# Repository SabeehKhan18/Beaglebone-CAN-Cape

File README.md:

# Beaglebone CAN Cape
Simple CAN cape for the Beaglebone Black

This is a CAN transceiver evaluation board that can be used to develop a CAN bus or even to sniff a vehicle's CAN bus. By using an SOIC-8 breakout board, and adjusting the pin jumpers provided on the cape, any 3.3V or 5V SOIC-8 CAN transceiver can be tested.
A demo of our project can be found on youtube:
https://youtu.be/FzIJ83zwgUM

## WARNING ##
Accessing your vehicle's CAN bus can be a dangerous endeavor. Reading the bus is typically not a problem, however sending messages can disrupt the operation of the vehicle, cause trouble codes, and potentially lead to undesired operation of the vehicle, up to and including moving under its own discretion. Needless to say, this can FATALLY INJURE YOU, so be careful. We are not responsible for any outcomes that the use of the provided hardware design or software may cause. There is no warranty.

## Installation Instructions ##

The installation of this project is relatively simple. First, begin by cloning the github repository:

`beagle$ git clone https://github.com/SabeehKhan18/Beaglebone-CAN-Cape.git`

 Be sure you have disabled the HDMI in /boot/uEnv.txt by uncommenting:

`dtb=am335x-boneblack-emmc-overlay.dtb`

If you have not previously done the above, you will need to reboot after uncommenting the line.

Next, run the installation script included in the repo. The installation script installs the linux package `can-utils` on the beaglebone. This package has the software necessary to make sense of the messages on the bus and provides a display interface:

`root@beagle$ cd Beaglebone-CAN-cape/`

`root@beagle$ ./install.sh`

Then, be sure you are operating as root, and then source the setup script. This will configure the pin muxes for dcan1, which operates on P9_24 and P9_26. It also uses P8_13 to control the CAN transceiver STANDBY pin. Then it sets up the interface can1. You must provide the bitrate of the CAN bus as an argument, replacing `BITRATE` in the command below. If you are developing your own network, you should know this value as you should have selected it. If you are attempting to sniff a production vehicle, your best bet is to start with 500000, which is representative of 500 kbps. If this doesn`t work, try a google search to see if you can find the bitrate:

`beagle$ source setup.sh BITRATE`

After the above steps complete successfully, the can1 interface should be up and running. You can confirm this by running:

`root@beagle$ ifconfig`

You should see an interface `can1` and, if you have connected to a bus and have entered the correct bitrate, you should see an RX count above 0.

If you have a can1 interface up and running, you now have a couple of can-utils you can use to view the messages. The first is:

`root@beagle$ candump can1`

This will dump all of the received CAN messages to the terminal.

If you want a more organized view, then cansniffer is your best bet. Run:

`root@beagle$ cansniffer can1 -c`

The cansniffer utility will display the messages received in the terminal as well, but it isn`t a scrolling list. When a message is received, and a previous message with that ID has already been received, the new data overwrites the old data. Further, the -c flag causes any differences in the data received from one message to the next to be highlighted in red.

## Hardware Instructions ##
To use the board and schematic files included in this repository, you will need to install EAGLE by Cadsoft. The freeware version is enough to open and edit this board. Simply copy the CAN-Cape directory to your EAGLE project directory, or change your EAGLE project directory to this repo on your machine. You will also need to include a library in your project, which is found in the Eagle-Libraries directory. You can find an EAGLE download here:

https://cadsoft.io/

The board can be printed by sending gerber files to a PCB fab company. I used the Sparkfun DRU and CAM processor in order to check the board and generate the gerber files. They can be found here:

https://www.sparkfun.com/tutorials/115

A list of components can be found in PartsList.ods. Feel free to modify the hardware design to accomodate any components you would like to use.

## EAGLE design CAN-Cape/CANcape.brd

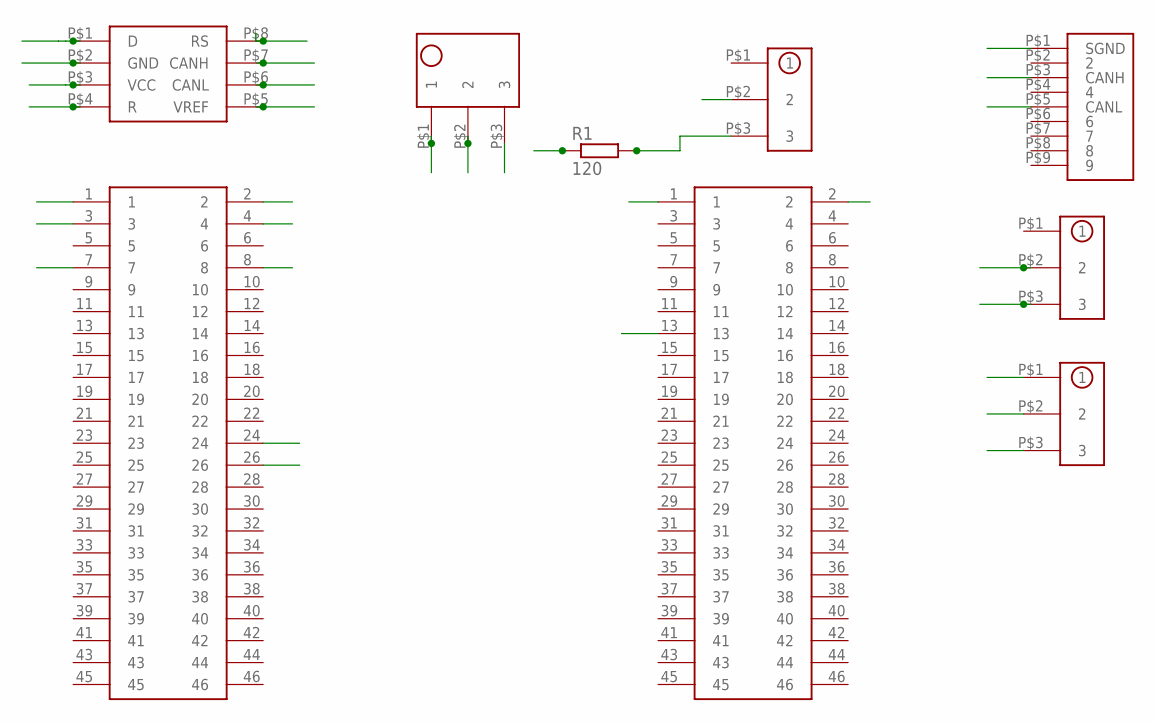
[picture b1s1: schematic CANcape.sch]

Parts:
R1: 120; 0207/15
U$1, U$2: 2X23_STACKABLE_HEADERS; 2X23_STACKABLE-HEADERS
U$3: TB-5.0-PT-3P
U$4, U$7, U$8: 1X3_HEADER
U$5: SOIC_BREAKOUT
U$6: DB9_BREAKOUT

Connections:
3.3V: U$1.3, U$1.4, U$5.P$5 (VREF), U$8.P$1 (1)
5V: U$1.7, U$1.8, U$8.P$3 (3)
CANH: U$3.P$1 (1), U$4.P$2 (2), U$5.P$7 (CANH), U$6.P$3 (CANH)
CANL: R1.1, U$3.P$2 (2), U$5.P$6 (CANL), U$6.P$5 (CANL)
DCAN1_RX: U$1.24, U$5.P$4 (R)
DCAN1_TX: U$1.26, U$5.P$1 (D)
GND: U$1.1, U$1.2, U$2.1, U$2.2, U$5.P$2 (GND), U$7.P$3 (3)
unnamed: R1.2, U$4.P$3 (3)
SGND: U$3.P$3 (3), U$6.P$1 (SGND), U$7.P$2 (2)
STANDBY: U$2.13, U$5.P$8 (RS)
TRAN_PWR: U$5.P$3 (VCC), U$8.P$2 (2)

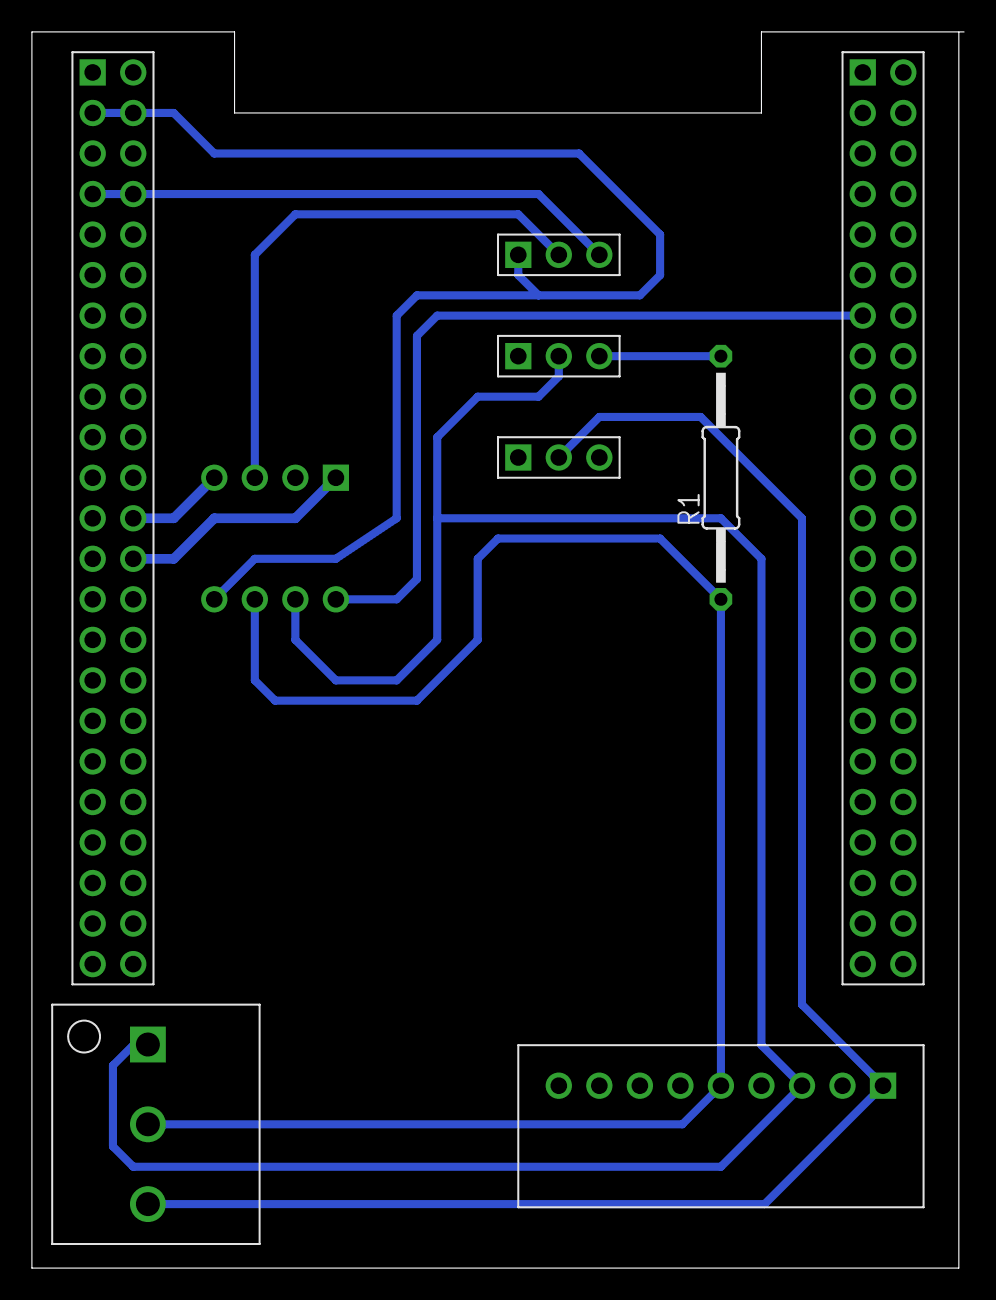
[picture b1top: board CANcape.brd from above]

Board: 2 copper layers, 58.4 x 77.5 mm, 9 parts (0 on the bottom side), 11 nets.

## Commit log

2016-10-13 initial commit of PL
2016-10-14 adding switch
2016-10-14 added library
2016-10-14 links to parts
2016-10-18 added package for soic
2016-10-18 added updated library
2016-10-18 added eagle project
2016-10-18 updated libraries:
2016-10-18 waiting on reformatting into mm of components
2016-10-20 Added SN65HVD320 device sym pac
2016-10-20 added board for david to look at and determine if good
2016-10-20 added 1x3 header part
2016-10-20 fixed soic sym, 1mm grid
2016-10-20 ooops
2016-10-20 added OBDII connector
2016-10-20 fixed sym for i/o
2016-10-20 added board. Ready for initial print
2016-10-21 added board files
2016-10-21 updated board to account for ethernet space conflict
2016-10-27 setting BB-DCAN1 dtc
2016-10-27 updated footprints and board design
2016-11-01 fixed setup
2016-11-03 instll instrc
2016-11-03 readme fix
2016-11-03 README.md fix
2016-11-03 more board work
2016-11-03 instruction
2016-11-04 board rev two is ready to go
2016-11-04 added outline and bottom layer files
2016-11-04 fix Read
2016-11-04 setup, dto rm
2016-11-08 removed the extra library
2016-11-09 setup installfiles
2016-11-09 install fix
2016-11-09 added README2
2016-11-10 rm unused brd
2016-11-10 added picture
2016-11-10 added png picture of cape
